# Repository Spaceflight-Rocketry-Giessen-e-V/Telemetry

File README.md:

# ASCENT Experimental Rocket Telemetry System

|</p> | </p></p>|
|---|---|
|<p align="center">[The Onboard System](/onboard/)</p>|<p align="center">[The Groundstation System](/groundstation/)</p>|

---

## Overview

The ASCENT telemetry system is part of the ASCENT flight computer of the student rocketry club [Spaceflight Rocketry Gießen e.V.](https://sprog-ev.de/en/), which is being developed for the PIPE and ARCHER experimental rockets.
This dual-frequency 169/869 MHz telemetry system based on Radiocrafts RC232 radio modules allows bidirectional data exchange between rockets and groundstations with a range of 20 km and a minimum data rate of 1.2 kbps.
The design can easily be adapted for uses outside of rocketry like Smart Home or RC.

## Basic Functionality

- Receiving flight data from the rocket
- Sending radio commands to the rocket
- Displaying live telemetry on a serial monitor or UI

## Actual Performance

In January 2026, we performed our first long range test over a distance of 2 km. Despite poor weather conditions and objects inside the first Fresnel zone, the received signal strength was on par with the theoretical maximum without any unaccounted losses. This test ruled out major design flaws.

This excellent performance was confirmed by multiple medium range tests.

In April 2026, the system was successfully tested on the PIPE 2 rocket to an altitude of 350 m and experienced no link issues during the whole flight.

---

## Repository Contents

This repository contains all files necessary to reproduce the telemetry system, including hardware, firmware, software, and documentation.

### 1. Antenna Hardware

So far, this repository includes [design files](/groundstation/antenna/helical/) and [assembly instructions](/docs/helical_antenna_assembly_manual.md) for our helical 869 MHz groundstation antenna.

We also do our own FDTD-simulations which can be found [here](groundstation/antenna/helical/Simulation/Helical_Antenna.m).

Currently, we are developing an 869 MHz QFH antenna.

### 2. Electronics Hardware

The telemetry system is based on separate [onboard](/onboard/pcb/) and [groundstation](/groundstation/pcb/) electronics.
The groundstation uses a modular approach with a [motherboard](/groundstation/pcb/Motherboard/) to which up to four [daughterboards](/groundstation/pcb/Daughterboard/) with radio modules can be connected.

The repository includes for each system the KiCad design files including custom component schematic, footprint, and 3D model libraries, the PDF schematic, the Gerber production files, the bill of material (BOM) and an interactive BOM (iBOM). 
Renderings, images, and 3D models of the electronics are also included.

The [onboard mounting structure](/onboard/mounting%20structure/), the [motherboard and daughterboard casings](/groundstation/casing/) are included separately.

### 3. Firmware

- [Onboard Firmware](/onboard/firmware/)
- [Groundstation Firmware](/groundstation/firmware/) 
- [Radiocrafts RC17xHP-RC232 Library](/libraries/Radiocrafts_RC17xxHP_RC232/)
- [Dynamic Package Codec (Encoding/Decoding) Library](/libraries/DynamicPacketCodec/)
- [Firmware Functions/Classes Reference](https://spaceflight-rocketry-giessen-e-v.github.io/Telemetry/)

### 4. Groundstation UI Software

[Python-based software](/groundstation/gui/) to display live telemetry data on a modern, minimalistic interface with the ability to store flight data and send radio commands. 

Widgets include a GNSS map view, a height plot over time, a acceleration plot over time, a battery voltage indicator with visual warnings, a connection quality indicator with visual warnings and a status event indicator.

### 5. Documentation

- [User Manual](/docs/user_manual.md) and [Operations Cheatsheet](/docs/operations_cheatsheet.md)
- [Design Overview/Rationals](/docs/design_overview.md)
- Documentation of the [Packet Structure](/docs/packet_structure.md) and the [Linkbudget Calculation](/docs/linkbudget.ipynb)
- [And more...](/docs/)

---

## Legal Notice

Please note that radio systems may be subject to local regulations. Ensure that any testing or deployment of these systems complies with national and regional laws regarding RF transmission. The project maintainers are not responsible for misuse or regulatory violations.  

## License

Copyright Spaceflight Rocketry Giessen e.V. 2026<br />
This source describes Open Hardware and is licensed under the CERN-OHL-S v2.<br />
You may redistribute and modify this source and make products using it under the terms of the [CERN-OHL-S v2 or any later version](LICENSE).<br />
This source is distributed WITHOUT ANY EXPRESS OR IMPLIED WARRANTY, INCLUDING OF MERCHANTABILITY, SATISFACTORY QUALITY AND FITNESS FOR A PARTICULAR PURPOSE. Please see the CERN-OHL-S v2 for applicable conditions.<br />
Source location: https://github.com/Spaceflight-Rocketry-Giessen-e-V/Telemetry<br />
As per CERN-OHL-S v2 section 4, should you produce hardware based on this source, you must where practicable maintain the Source Location in its documentation or license information.<br />

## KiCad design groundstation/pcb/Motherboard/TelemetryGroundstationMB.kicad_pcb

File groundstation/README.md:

# The Groundstation System

- [Motherboard Electronics Hardware](/groundstation/pcb/Motherboard/)
    - [KiCad Design Files](/groundstation/pcb/Motherboard/)
    - [PDF Schematic](/groundstation/pcb/Motherboard/TelemetryGroundstationMB_Schematic.pdf)
    - [Interactive Schematic / iBOM](/groundstation/pcb/Motherboard/TelemetryGroundstationMB_iBOM.html)
    - [BOM](/groundstation/pcb/Motherboard/TelemetryGroundstationMB_BOM.csv)
    - [Gerber Files](/groundstation/pcb/Motherboard/Production%20Files/)
    - [PCB 3D Model](/groundstation/pcb/Motherboard/TelemetryGroundstationMB.step)
    - [PCB Images](/groundstation/pcb/Motherboard/images/)
- [Daughterboard Electronics Hardware](/groundstation/pcb/Daughterboard/)
    - [KiCad Design Files](/groundstation/pcb/Daughterboard/)
    - [PDF Schematic](/groundstation/pcb/Daughterboard/TelemetryGroundstationDB_Schematic.pdf)
    - [Interactive Schematic / iBOM](/groundstation/pcb/Daughterboard/TelemetryGroundstationDB_iBOM.html)
    - [BOM](/groundstation/pcb/Daughterboard/TelemetryGroundstationDB_BOM.csv)
    - [Gerber Files](/groundstation/pcb/Daughterboard/Production%20Files/)
    - [PCB 3D Model](/groundstation/pcb/Daughterboard/TelemetryGroundstationDB.step)
    - [PCB Images](/groundstation/pcb/Daughterboard/images/)
- [Electronics Casings](/groundstation/casing/)
    - [Motherboard Casing](/groundstation/casing/Motherboard)
    - [Daughterboard Casing](/groundstation/casing/Daughterboard)
- [Firmware](/groundstation/firmware/)
- [869 MHz Helical Antenna](/groundstation/antenna/helical/)
    - [Design Files](/groundstation/antenna/helical/)
    - [Design Guide](/docs/helical_antenna_design_guide.ipynb)
    - [Assembly Manual](/docs/helical_antenna_assembly_manual.md)
    - [Antenna 3D Model](/groundstation/antenna/helical/Antenna%20Assembly.step)
    - [Antenna Images](/groundstation/antenna/helical/images/)
    - [Simulation](/groundstation/antenna/helical/Simulation/)
    - [Simulation Guide](/docs/helical_antenna_simulation_guide.md)
- [Serial Monitor Configuration File](/groundstation/Coolterm_SerialMonitor_Settings.CoolTermSettings)
- [Graphical User Interface](/groundstation/gui/)

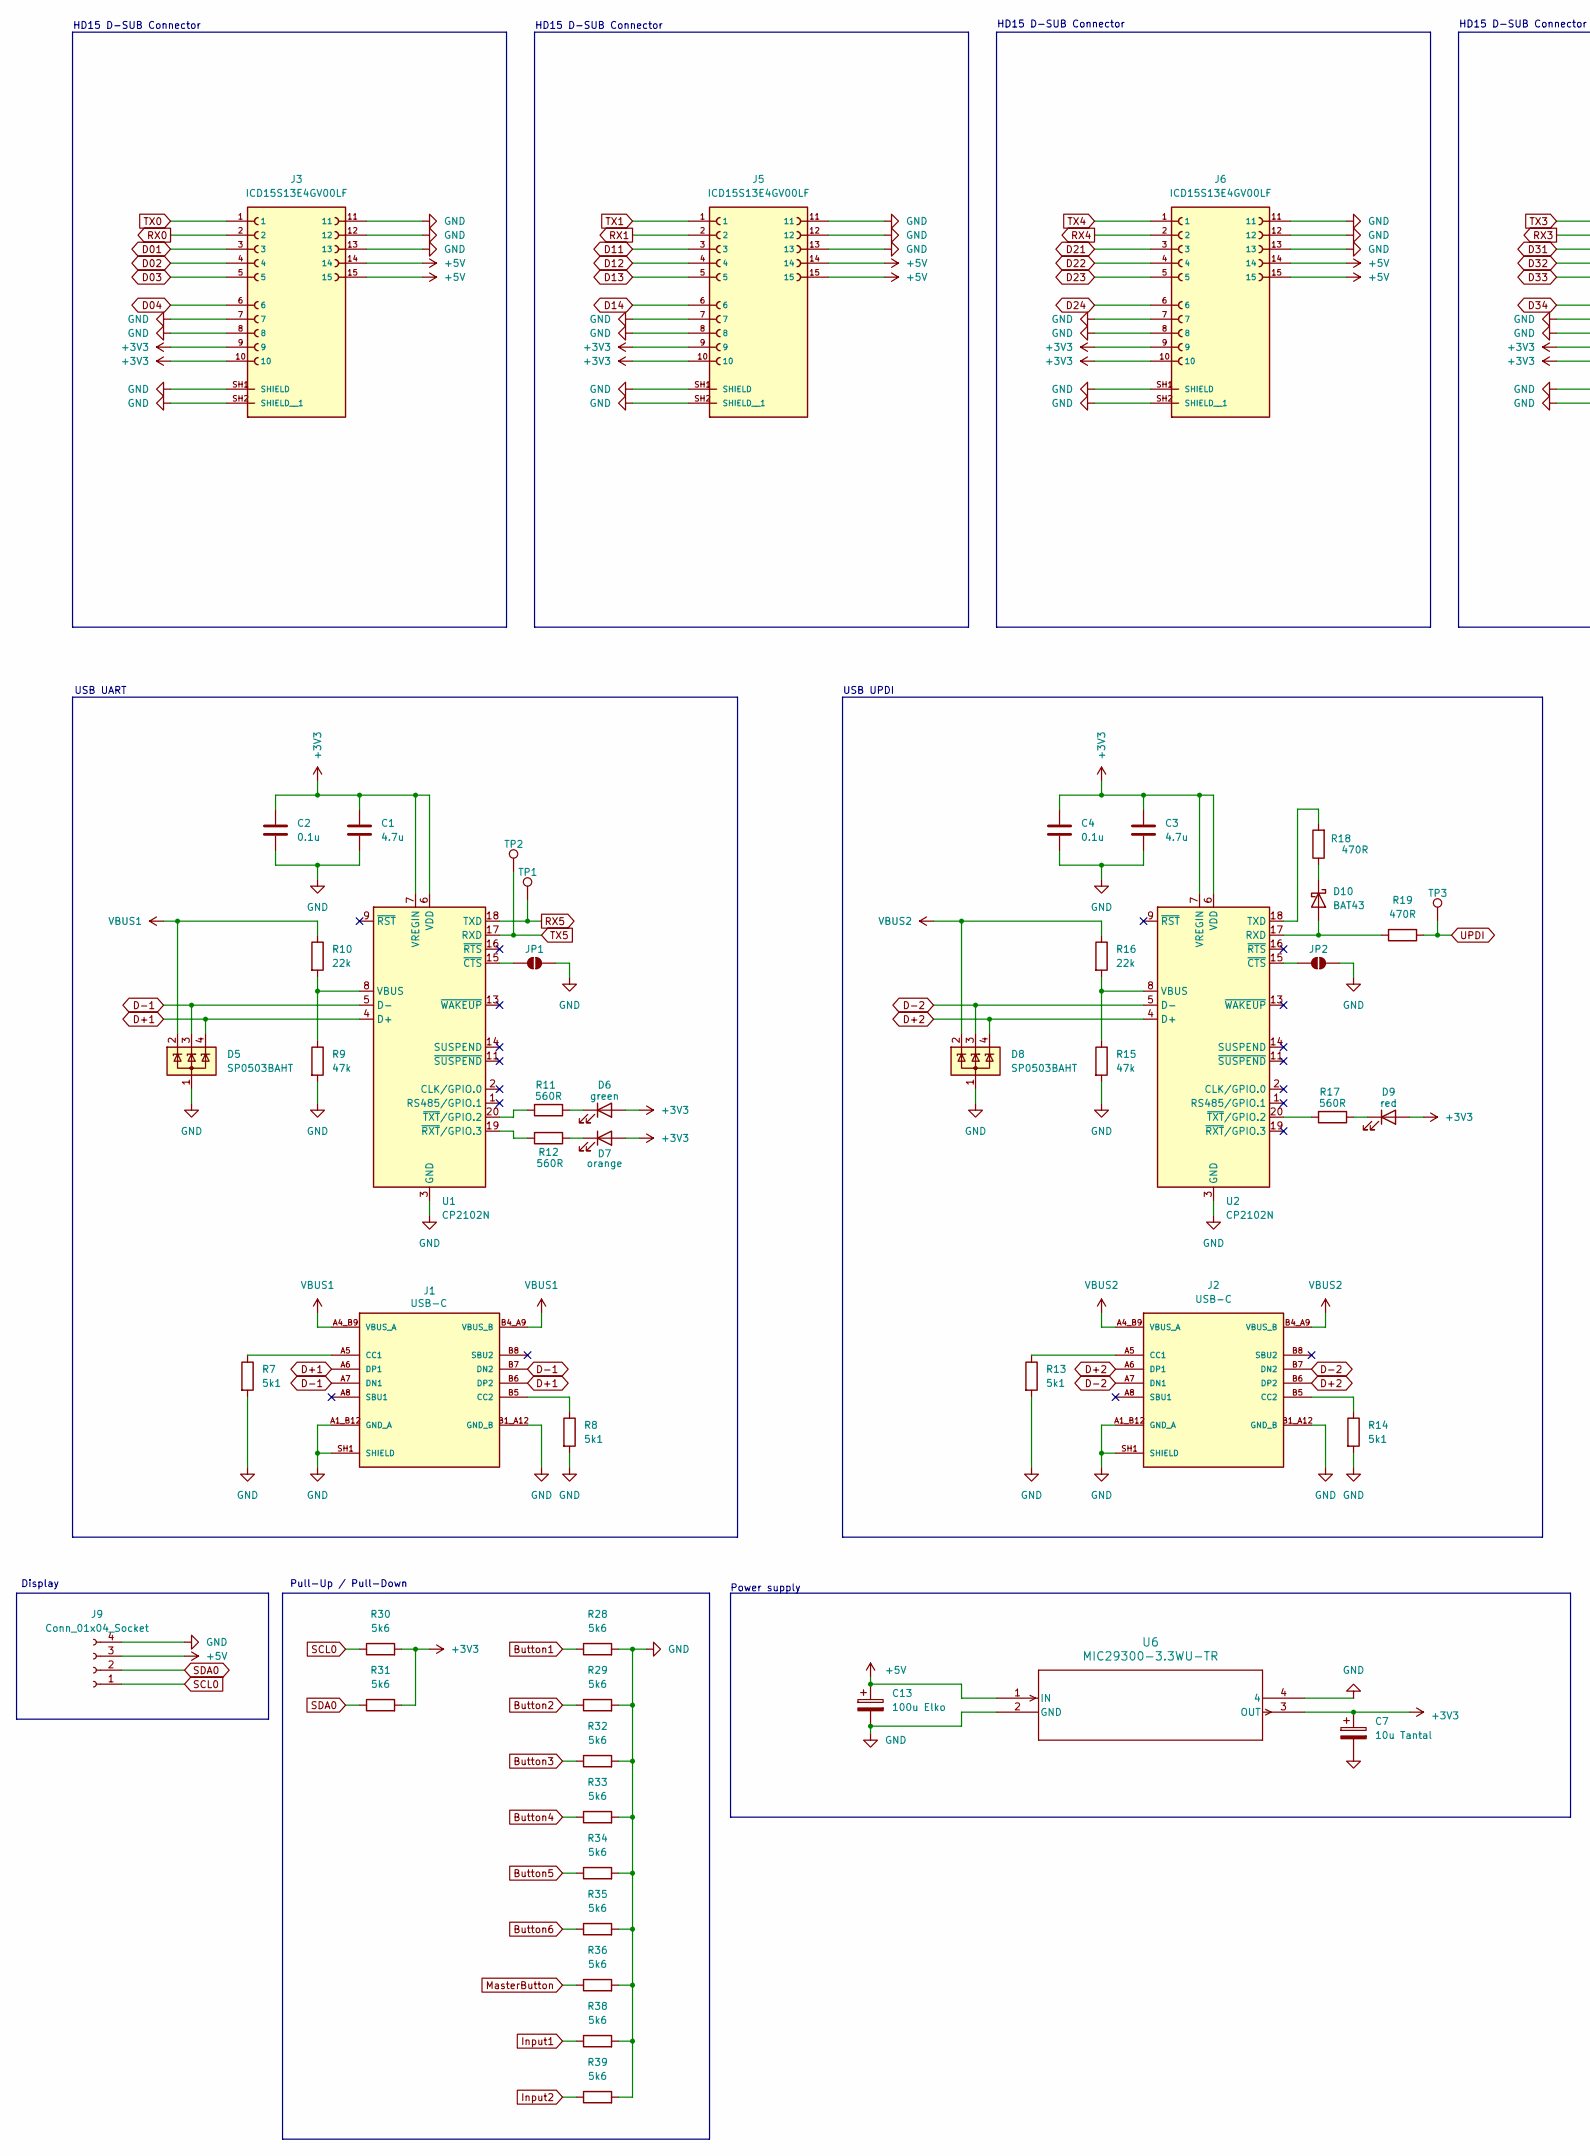
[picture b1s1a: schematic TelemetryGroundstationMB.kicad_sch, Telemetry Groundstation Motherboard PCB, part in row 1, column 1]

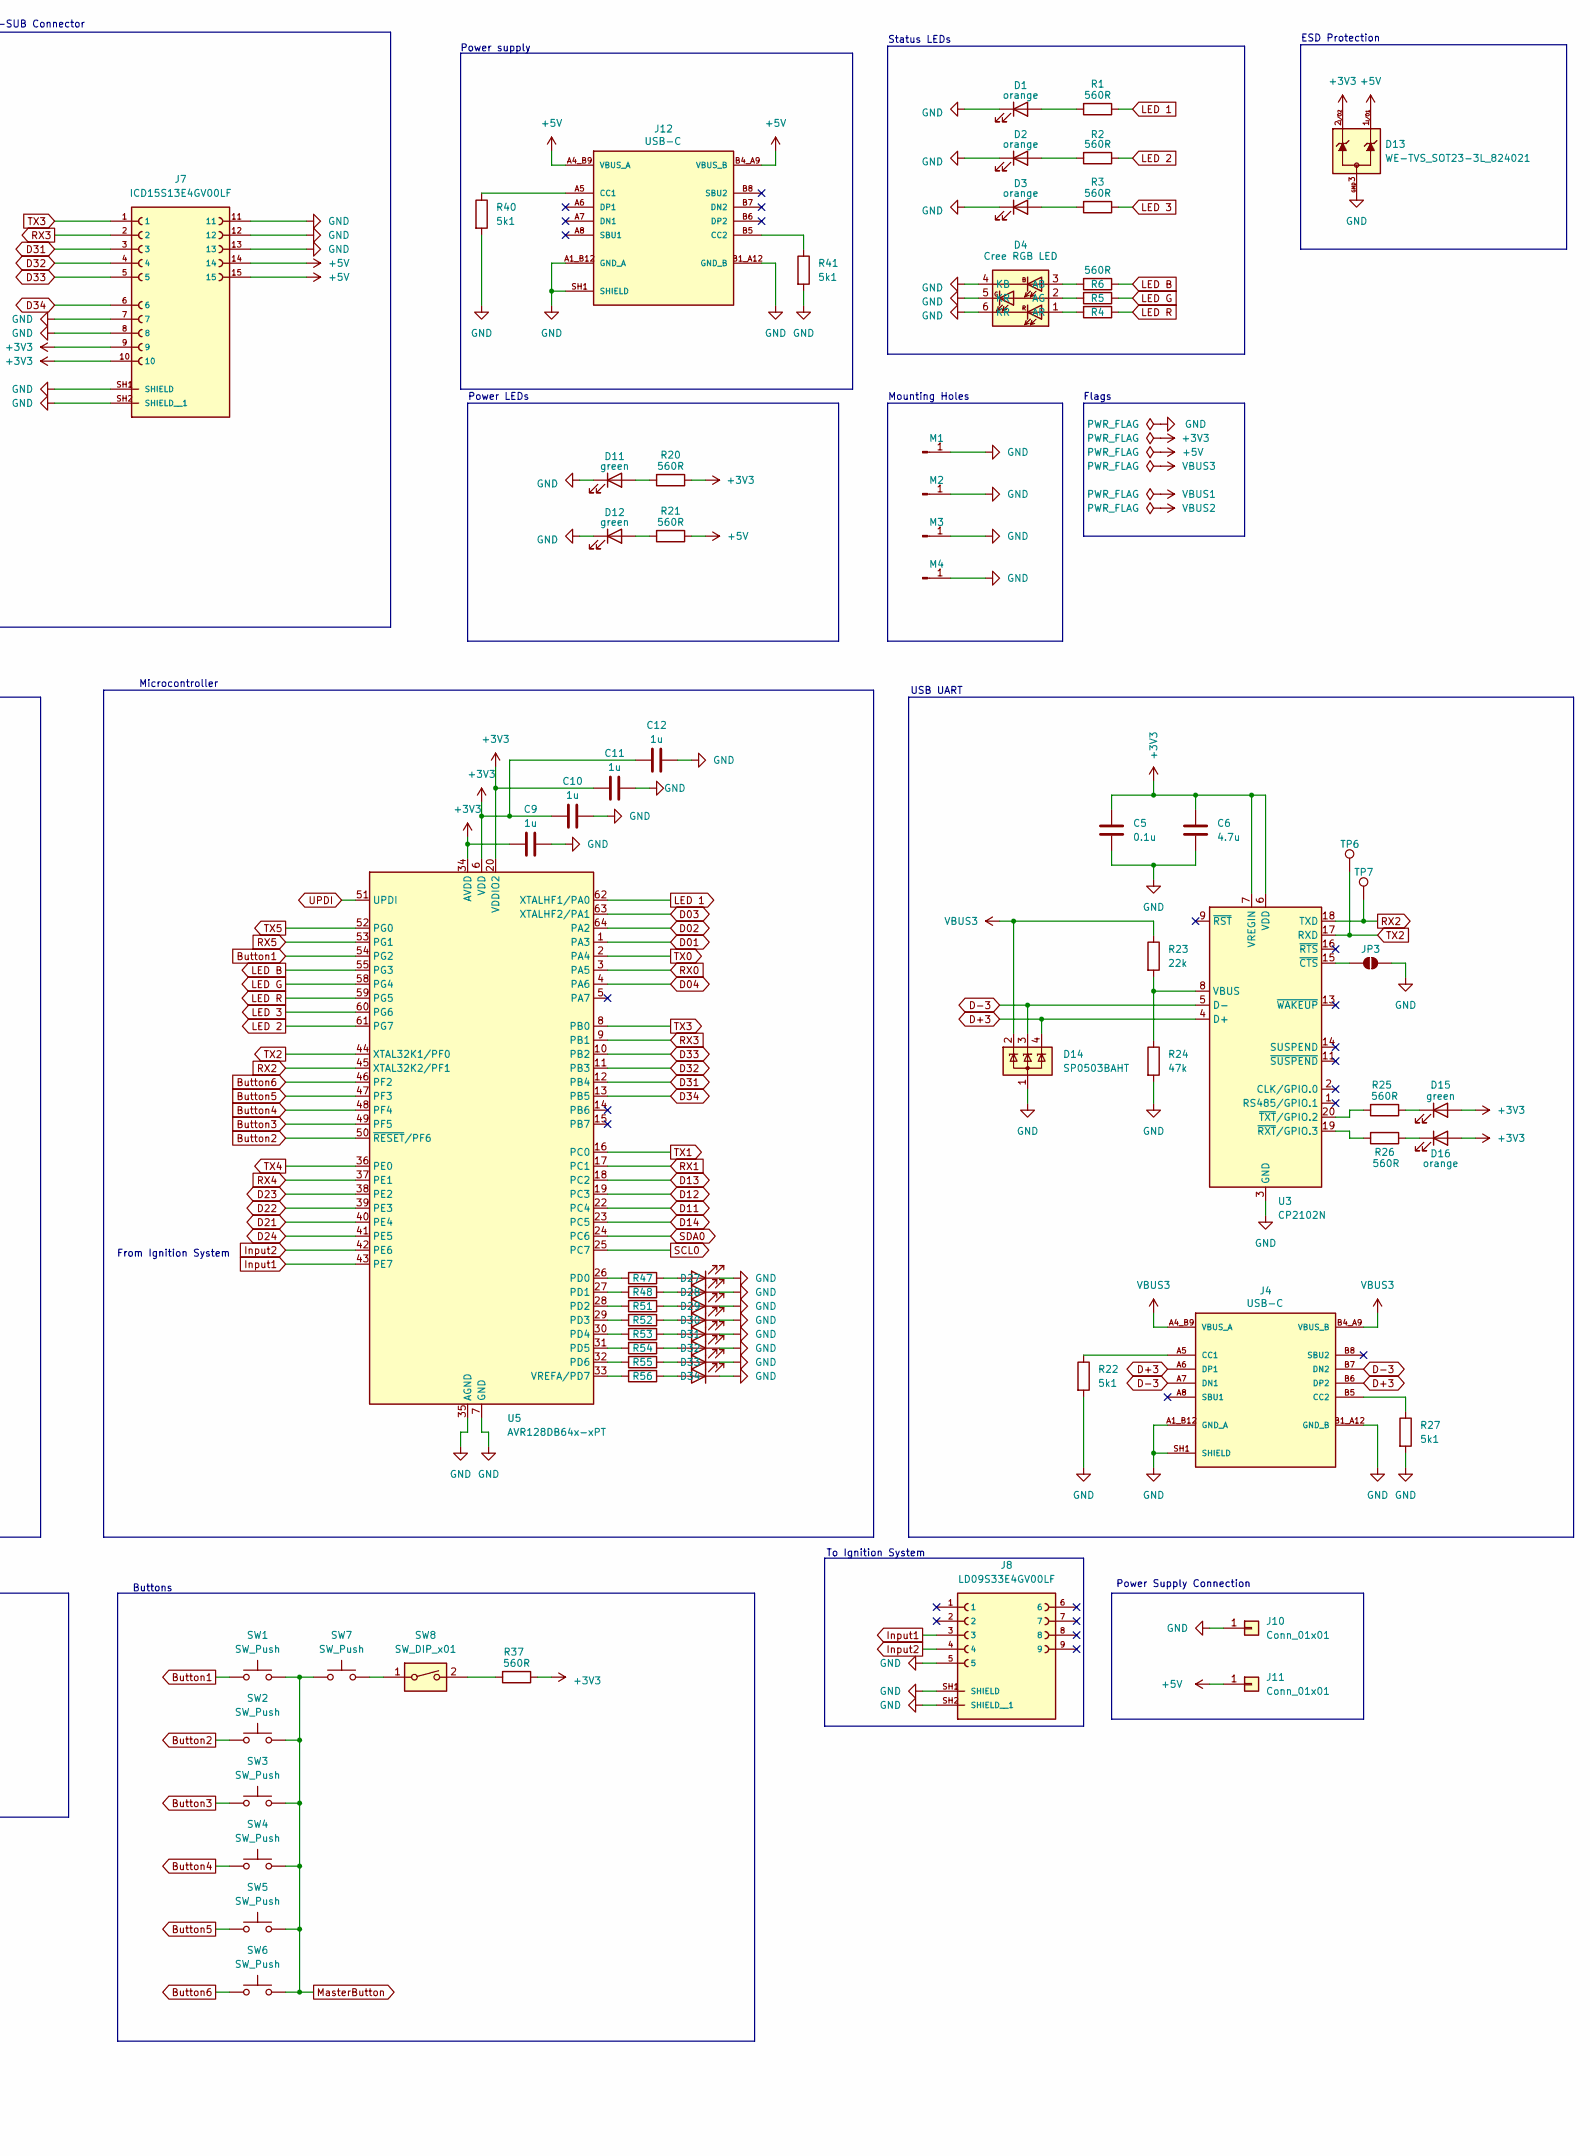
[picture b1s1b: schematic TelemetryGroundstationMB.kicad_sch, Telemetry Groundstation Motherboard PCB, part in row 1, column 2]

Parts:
C1, C3, C6: 4.7u; C_0805_2012Metric_Pad1.18x1.45mm_HandSolder
C2, C4, C5: 0.1u; C_0805_2012Metric_Pad1.18x1.45mm_HandSolder
C7: 10u Tantal; CAPMP3216X180N
C9, C10, C11, C12: 1u; C_0805_2012Metric_Pad1.18x1.45mm_HandSolder
C13: 100u Elko; CP_Radial_D6.3mm_P2.50mm
D1, D2, D3, D7, D16, D27, D28, D29, D30, D31, D32, D33, D34: orange; LED_0805_2012Metric_Pad1.15x1.40mm_HandSolder
D4: Cree RGB LED
D5, D8, D14: SP0503BAHT; SOT-143
D6, D11, D12, D15: green; LED_0805_2012Metric_Pad1.15x1.40mm_HandSolder
D9: red; LED_0805_2012Metric_Pad1.15x1.40mm_HandSolder
D10: BAT43; D_SOD-123
D13: WE-TVS_SOT23-3L_824021; SOT-23-3
J1, J2, J4, J12: USB-C; GCT_USB4216-03-A_REVA; PARTREV A; DigiKey_Part_Number 2073-USB4215-03-ACT-ND
J3, J5, J6, J7: ICD15S13E4GV00LF; AMPHENOL_ICD15S13E4GV00LF[1]; PARTREV G
J8: LD09S33E4GV00LF; AMPHENOL_LD09S33E4GV00LF; PARTREV B
J9: Conn_01x04_Socket; PinSocket_1x04_P2.54mm_Vertical
J10: Conn_01x01; Banana_CT3151-0
J11: Conn_01x01; Banana_CT3151-2
JP1, JP2, JP3: SolderJumper_2_Open; Solder Jumper
M1, M2, M3, M4: M4 Mounting Hole
R1, R2, R3, R4, R5, R6, R11, R12, R17, R20, R21, R25, R26, R37, R47, R48, R51, R52, R53, R54, R55, R56: 560R; R_0805_2012Metric_Pad1.20x1.40mm_HandSolder
R7, R8, R13, R14, R22, R27, R40, R41: 5k1; R_0805_2012Metric_Pad1.20x1.40mm_HandSolder
R9, R15, R24: 47k; R_0805_2012Metric_Pad1.20x1.40mm_HandSolder
R10, R16, R23: 22k; R_0805_2012Metric_Pad1.20x1.40mm_HandSolder
R18, R19: 470R; R_0805_2012Metric_Pad1.20x1.40mm_HandSolder
R28, R29, R30, R31, R32, R33, R34, R35, R36, R38, R39: 5k6; R_0805_2012Metric_Pad1.20x1.40mm_HandSolder
SW1, SW2, SW3, SW4, SW5, SW6, SW7: SW_Push; PinSocket_1x02_P2.54mm_Vertical
SW8: SW_DIP_x01; PinSocket_1x02_P2.54mm_Vertical
TP1, TP2, TP3, TP6, TP7: TestPoint; Test Point
U1, U2, U3: CP2102N; QFN20_CP2102N_SIL
U5: AVR128DB64x-xPT; TQFP-64_10x10mm_P0.5mm
U6: MIC29300-3.3WU-TR; MIC29300

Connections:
+3V3: C1.1, C2.1, C3.1, C4.1, C5.1, C6.1, C7.1, C9.1, C10.1, C11.2, C12.2, D6.2 (A), D7.2 (A), D9.2 (A), D13.2, D15.2 (A), D16.2 (A), J3.9, J3.10, J5.9, J5.10, J6.9, J6.10, J7.9, J7.10, R20.1, R30.2, R31.2, R37.1, U1.6 (VDD), U1.7 (VREGIN), U2.6 (VDD), U2.7 (VREGIN), U3.6 (VDD), U3.7 (VREGIN), U5.6 (VDD), U5.20 (VDDIO2), U5.34 (AVDD), U5.56 (VDD), U6.3 (OUT)
+5V: C13.1, D13.1, J3.14, J3.15, J5.14, J5.15, J6.14, J6.15, J7.14, J7.15, J9.3, J11.1, J12.A4_B9 (VBUS_A), J12.B4_A9 (VBUS_B), R21.1, U6.1 (IN)
Button1: R28.1, SW1.1, U5.54 (PG2)
Button2: R29.1, SW2.1, U5.50 (~RESET/PF6)
Button3: R32.1, SW3.1, U5.49 (PF5)
Button4: R33.1, SW4.1, U5.48 (PF4)
Button5: R34.1, SW5.1, U5.47 (PF3)
Button6: R35.1, SW6.1, U5.46 (PF2)
D01: J3.3, U5.1 (PA3)
D02: J3.4, U5.64 (PA2)
D03: J3.5, U5.63 (XTALHF2/PA1)
D04: J3.6, U5.4 (PA6)
D11: J5.3, U5.22 (PC4)
D12: J5.4, U5.19 (PC3)
D13: J5.5, U5.18 (PC2)
D14: J5.6, U5.23 (PC5)
D21: J6.3, U5.40 (PE4)
D22: J6.4, U5.39 (PE3)
D23: J6.5, U5.38 (PE2)
D24: J6.6, U5.41 (PE5)
D31: J7.3, U5.12 (PB4)
D32: J7.4, U5.11 (PB3)
D33: J7.5, U5.10 (PB2)
D34: J7.6, U5.13 (PB5)
D+1: D5.4 (K), J1.A6 (DP1), J1.B6 (DP2), U1.4 (D+)
D+2: D8.4 (K), J2.A6 (DP1), J2.B6 (DP2), U2.4 (D+)
D+3: D14.4 (K), J4.A6 (DP1), J4.B6 (DP2), U3.4 (D+)
D-1: D5.3 (K), J1.A7 (DN1), J1.B7 (DN2), U1.5 (D-)
D-2: D8.3 (K), J2.A7 (DN1), J2.B7 (DN2), U2.5 (D-)
D-3: D14.3 (K), J4.A7 (DN1), J4.B7 (DN2), U3.5 (D-)
GND: C1.2, C2.2, C3.2, C4.2, C5.2, C6.2, C7.2, C9.2, C10.2, C11.1, C12.1, C13.2, D1.1 (K), D2.1 (K), D3.1 (K), D4.4 (KB), D4.5 (KR), D4.6 (KR), D5.1 (A), D8.1 (A), D11.1 (K), D12.1 (K), D13.3, D14.1 (A), D27.1 (K), D28.1 (K), D29.1 (K), D30.1 (K), D31.1 (K), D32.1 (K), D33.1 (K), D34.1 (K), J1.A1_B12 (GND_A), J1.B1_A12 (GND_B), J1.SH1 (SHIELD), J1.SH2 (SHIELD), J1.SH3 (SHIELD), J1.SH4 (SHIELD), J2.A1_B12 (GND_A), J2.B1_A12 (GND_B), J2.SH1 (SHIELD), J2.SH2 (SHIELD), J2.SH3 (SHIELD), J2.SH4 (SHIELD), J3.7, J3.8, J3.11, J3.12, J3.13, J3.SH1 (SHIELD), J3.SH2 (SHIELD__1), J4.A1_B12 (GND_A), J4.B1_A12 (GND_B), J4.SH1 (SHIELD), J4.SH2 (SHIELD), J4.SH3 (SHIELD), J4.SH4 (SHIELD), J5.7, J5.8, J5.11, J5.12, J5.13, J5.SH1 (SHIELD), J5.SH2 (SHIELD__1), J6.7, J6.8, J6.11, J6.12, J6.13, J6.SH1 (SHIELD), J6.SH2 (SHIELD__1), J7.7, J7.8, J7.11, J7.12, J7.13, J7.SH1 (SHIELD), J7.SH2 (SHIELD__1), J8.5, J8.SH1 (SHIELD), J8.SH2 (SHIELD__1), J9.4, J10.1, J12.A1_B12 (GND_A), J12.B1_A12 (GND_B), J12.SH1 (SHIELD), J12.SH2 (SHIELD), J12.SH3 (SHIELD), J12.SH4 (SHIELD), JP1.2 (B), JP2.2 (B), JP3.2 (B), M1.1, M2.1, M3.1, M4.1, R7.2, R8.2, R9.2, R13.2, R14.2, R15.2, R22.2, R24.2, R27.2, R28.2, R29.2, R32.2, R33.2, R34.2, R35.2, R36.2, R38.2, R39.2, R40.2, R41.2, U1.3 (GND), U1.12 (GND), U1.21 (GND), U2.3 (GND), U2.12 (GND), U2.21 (GND), U3.3 (GND), U3.12 (GND), U3.21 (GND), U5.7 (GND), U5.21 (GND), U5.35 (AGND), U5.57 (GND), U6.2 (GND), U6.4, U6.5 (4), U6.6 (4)
Input1: J8.3, R38.1, U5.43 (PE7)
Input2: J8.4, R39.1, U5.42 (PE6)
LED 1: R1.1, U5.62 (XTALHF1/PA0)
LED 2: R2.1, U5.61 (PG7)
LED 3: R3.1, U5.60 (PG6)
LED B: R6.1, U5.55 (PG3)
LED G: R5.1, U5.58 (PG4)
LED R: R4.1, U5.59 (PG5)
MasterButton: R36.1, SW1.2, SW2.2, SW3.2, SW4.2, SW5.2, SW6.2, SW7.1
unnamed: D1.2 (A), R1.2
unnamed: D2.2 (A), R2.2
unnamed: D3.2 (A), R3.2
unnamed: D4.3 (AB), R6.2
unnamed: D4.2 (AG), R5.2
unnamed: D4.1 (AR), R4.2
unnamed: D6.1 (K), R11.1
unnamed: D7.1 (K), R12.1
unnamed: D9.1 (K), R17.1
unnamed: D10.2 (A), R19.2, U2.17 (RXD)
unnamed: D10.1 (K), R18.1
unnamed: D11.2 (A), R20.2
unnamed: D12.2 (A), R21.2
unnamed: D15.1 (K), R25.1
unnamed: D16.1 (K), R26.1
unnamed: D27.2 (A), R47.1
unnamed: D28.2 (A), R48.1
unnamed: D29.2 (A), R51.1
unnamed: D30.2 (A), R52.1
unnamed: D31.2 (A), R53.1
unnamed: D32.2 (A), R54.1
unnamed: D33.2 (A), R55.1
unnamed: D34.2 (A), R56.1
unnamed: J1.A5 (CC1), R7.1
unnamed: J1.B5 (CC2), R8.1
unnamed: J2.A5 (CC1), R13.1
unnamed: J2.B5 (CC2), R14.1
unnamed: J4.A5 (CC1), R22.1
unnamed: J4.B5 (CC2), R27.1
unnamed: J12.A5 (CC1), R40.1
unnamed: J12.B5 (CC2), R41.1
unnamed: JP1.1 (A), U1.15 (~CTS)
unnamed: JP2.1 (A), U2.15 (~CTS)
unnamed: JP3.1 (A), U3.15 (~CTS)
unnamed: R37.2, SW8.2
unnamed: SW7.2, SW8.1
unnamed: R9.1, R10.2, U1.8 (VBUS)
unnamed: R12.2, U1.19 (~RXT/GPIO.3)
unnamed: R11.2, U1.20 (~TXT/GPIO.2)
unnamed: R18.2, U2.18 (TXD)
unnamed: R15.1, R16.2, U2.8 (VBUS)
unnamed: R17.2, U2.20 (~TXT/GPIO.2)
unnamed: R23.2, R24.1, U3.8 (VBUS)
unnamed: R26.2, U3.19 (~RXT/GPIO.3)
unnamed: R25.2, U3.20 (~TXT/GPIO.2)
unnamed: R47.2, U5.26 (PD0)
unnamed: R48.2, U5.27 (PD1)
unnamed: R51.2, U5.28 (PD2)
unnamed: R52.2, U5.29 (PD3)
unnamed: R53.2, U5.30 (PD4)
unnamed: R54.2, U5.31 (PD5)
unnamed: R55.2, U5.32 (PD6)
unnamed: R56.2, U5.33 (VREFA/PD7)
RX0: J3.2, U5.3 (PA5)
RX1: J5.2, U5.17 (PC1)
RX2: TP7.1, U3.18 (TXD), U5.45 (XTAL32K2/PF1)
RX3: J7.2, U5.9 (PB1)
RX4: J6.2, U5.37 (PE1)
RX5: TP1.1, U1.18 (TXD), U5.53 (PG1)
SCL0: J9.1, R30.1, U5.25 (PC7)
SDA0: J9.2, R31.1, U5.24 (PC6)
TX0: J3.1, U5.2 (PA4)
TX1: J5.1, U5.16 (PC0)
TX2: TP6.1, U3.17 (RXD), U5.44 (XTAL32K1/PF0)
TX3: J7.1, U5.8 (PB0)
TX4: J6.1, U5.36 (PE0)
TX5: TP2.1, U1.17 (RXD), U5.52 (PG0)
UPDI: R19.1, TP3.1, U5.51 (UPDI)
VBUS1: D5.2 (K), J1.A4_B9 (VBUS_A), J1.B4_A9 (VBUS_B), R10.1
VBUS2: D8.2 (K), J2.A4_B9 (VBUS_A), J2.B4_A9 (VBUS_B), R16.1
VBUS3: D14.2 (K), J4.A4_B9 (VBUS_A), J4.B4_A9 (VBUS_B), R23.1

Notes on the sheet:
HD15 D-SUB Connector
Power Supply Connection
Pull-Up / Pull-Down
Power supply
Microcontroller
Flags
USB UPDI
USB UART
Status LEDs
Mounting Holes
Power LEDs
Display
ESD Protection
To Ignition System
From Ignition System
Buttons

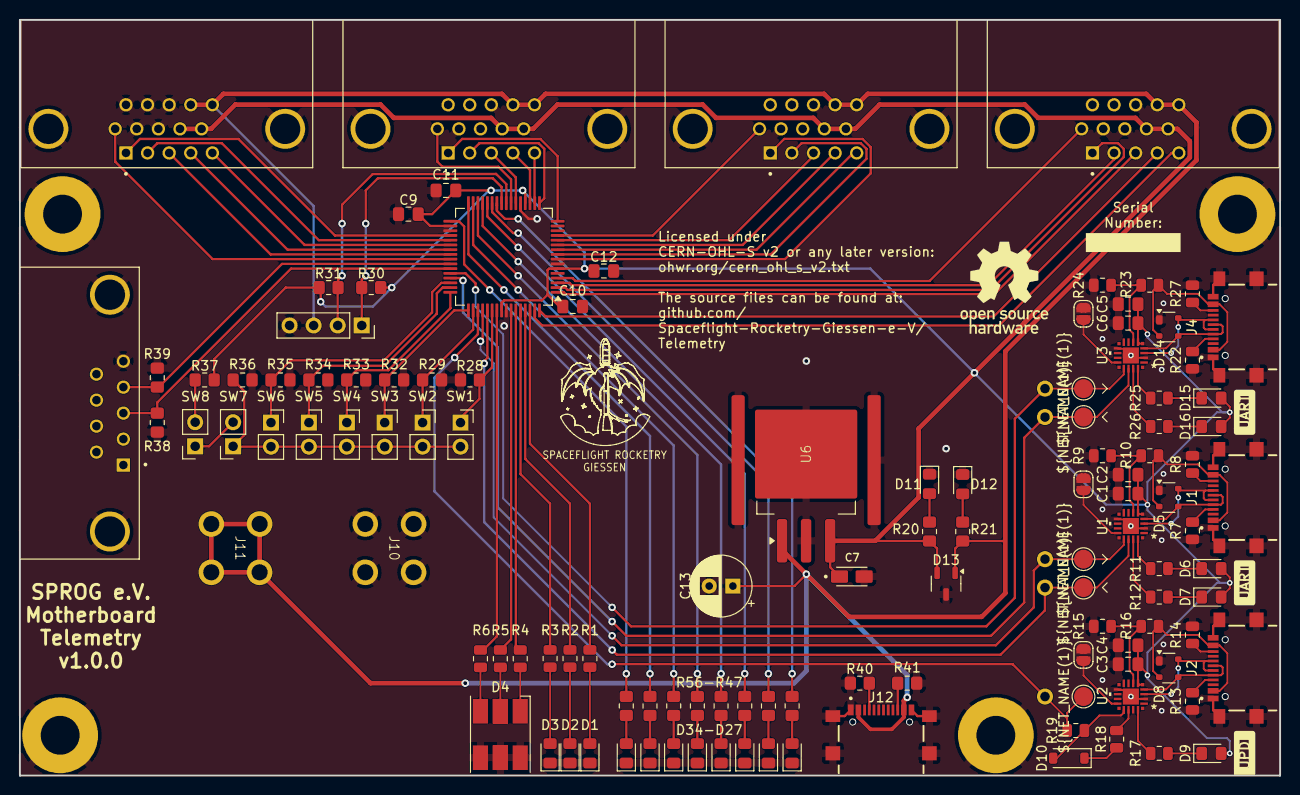
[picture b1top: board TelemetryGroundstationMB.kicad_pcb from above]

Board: 2 copper layers, 133.0 x 79.8 mm, 122 parts (0 on the bottom side), 111 nets.

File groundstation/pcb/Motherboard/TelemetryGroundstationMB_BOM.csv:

"Reference","Qty","Value","Footprint","DNP","Purchase-URL"
"C1,C3,C6","3","4.7 uF","Capacitor_SMD:C_0805_2012Metric_Pad1.18x1.45mm_HandSolder","",""
"C2,C4,C5","3","0.1 uF","Capacitor_SMD:C_0805_2012Metric_Pad1.18x1.45mm_HandSolder","",""
"C7","1","10uF Tantal","Footprints:CAPMP3216X180N","",""
"C9,C10,C11,C12","4","1 uF","Capacitor_SMD:C_0805_2012Metric_Pad1.18x1.45mm_HandSolder","","https://www.digikey.de/de/products/detail/samsung-electro-me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"
"C13","1","100uF Elko","Capacitor_THT:CP_Radial_D6.3mm_P2.50mm","",""
"D1,D2,D3,D7,D16,D27,D28,D29,D30,D31,D32,D33,D34","13","orange","LED_SMD:LED_0805_2012Metric_Pad1.15x1.40mm_HandSolder","","https://www.digikey.de/de/products/detail/liteon/LTST-C170KF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"
"D4","1","Cree RGB LED","Footprints:Cree RGB LED","",""
"D5,D8,D14","3","SP0503BAHT","Package_TO_SOT_SMD:SOT-143","",""
"D6,D11,D12,D15","4","green","LED_SMD:LED_0805_2012Metric_Pad1.15x1.40mm_HandSolder","",""
"D9","1","red","LED_SMD:LED_0805_2012Metric_Pad1.15x1.40mm_HandSolder","",""
"D10","1","BAT43","Diode_SMD:D_SOD-123","",""
"D13","1","WE-TVS_SOT23-3L_824021","Package_TO_SOT_SMD:SOT-23-3","",""
"J1,J2,J4,J12","4","USB-C","Footprints:GCT_USB4216-03-A_REVA","",""
"J3,J5,J6,J7","4","ICD15S13E4GV00LF","Footprints:AMPHENOL_ICD15S13E4GV00LF[1]","",""
"J8","1","LD09S33E4GV00LF","Footprints:AMPHENOL_LD09S33E4GV00LF","",""
"J9","1","Conn_01x04_Socket","Connector_PinSocket_2.54mm:PinSocket_1x04_P2.54mm_Vertical","",""
"J10,J11","2","Conn_01x01","Footprints:Banana_CT3151-0","",""
"M1,M2,M3,M4","4","M4 Mounting Hole","Footprints:M4 Mounting Hole","",""
"R1,R2,R3,R4,R5,R6,R11,R12,R17,R20,R21,R25,R26,R37,R47,R48,R51,R52,R53,R54,R55,R56","22","560 Ohm","Resistor_SMD:R_0805_2012Metric_Pad1.20x1.40mm_HandSolder","","https://www.digikey.de/de/products/detail/yageo/RC0805JR-072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"
"R7,R8,R13,R14,R22,R27,R40,R41","8","5k1","Resistor_SMD:R_0805_2012Metric_Pad1.20x1.40mm_HandSolder","",""
"R9,R15,R24","3","47k","Resistor_SMD:R_0805_2012Metric_Pad1.20x1.40mm_HandSolder","",""
"R10,R16,R23","3","22k","Resistor_SMD:R_0805_2012Metric_Pad1.20x1.40mm_HandSolder","",""
"R18,R19","2","470 Ohm","Resistor_SMD:R_0805_2012Metric_Pad1.20x1.40mm_HandSolder","",""
"R28,R29,R30,R31,R32,R33,R34,R35,R36,R38,R39","11","5k6","Resistor_SMD:R_0805_2012Metric_Pad1.20x1.40mm_HandSolder","",""
"SW1,SW2,SW3,SW4,SW5,SW6,SW7","7","SW_Push","Connector_PinSocket_2.54mm:PinSocket_1x02_P2.54mm_Vertical","",""
"SW8","1","SW_DIP_x01","Connector_PinSocket_2.54mm:PinSocket_1x02_P2.54mm_Vertical","",""
"TP1,TP2,TP3,TP6,TP7","5","TestPoint","Footprints:Test Point","",""
"U1,U2,U3","3","CP2102N","Footprints:QFN20_CP2102N_SIL","",""
"U5","1","AVR128DB64x-xPT","Package_QFP:TQFP-64_10x10mm_P0.5mm","","https://www.digikey.de/de/products/detail/microchip-technolo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"
"U6","1","MIC29300-3.3WU-TR","Footprints:MIC29300","",""

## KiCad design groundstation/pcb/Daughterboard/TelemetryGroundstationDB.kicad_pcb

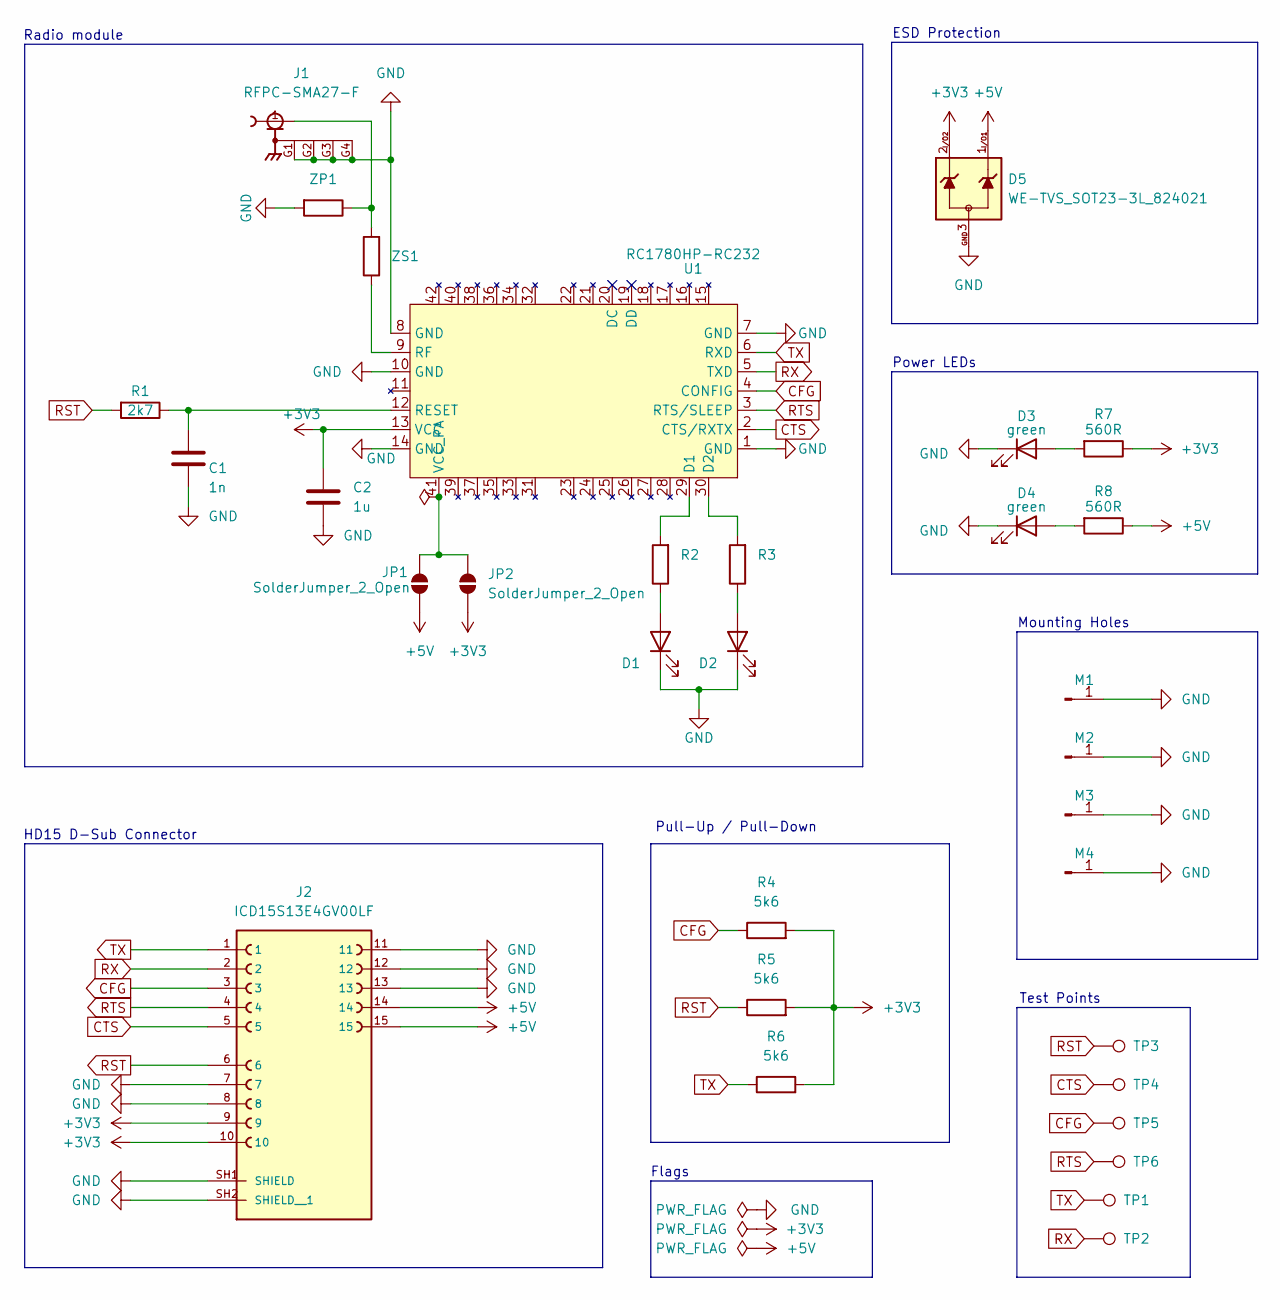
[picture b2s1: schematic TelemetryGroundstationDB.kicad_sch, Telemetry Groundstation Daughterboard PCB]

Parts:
C1: 1n; C_0805_2012Metric_Pad1.18x1.45mm_HandSolder
C2: 1u; C_0805_2012Metric_Pad1.18x1.45mm_HandSolder
D1, D3, D4: green; LED_0805_2012Metric_Pad1.15x1.40mm_HandSolder
D2: yellow; LED_0805_2012Metric_Pad1.15x1.40mm_HandSolder
D5: WE-TVS_SOT23-3L_824021; SOT-23-3
J1: RFPC-SMA27-F; GRADCONN_RFPC-SMA27-F; PARTREV 1.0; DigiKey_Part_Number 2073-RFPC-SMA27-F-ND
J2: ICD15S13E4GV00LF; AMPHENOL_ICD15S13E4GV00LF[1]; PARTREV G
JP1, JP2: SolderJumper_2_Open; Solder Jumper
M1, M2, M3, M4: M4 Mounting Hole
R1: 2k7; R_0805_2012Metric_Pad1.20x1.40mm_HandSolder
R2, R3, R7, R8: 560R; R_0805_2012Metric_Pad1.20x1.40mm_HandSolder
R4, R5, R6: 5k6; R_0805_2012Metric_Pad1.20x1.40mm_HandSolder
TP1, TP2, TP3, TP4, TP5, TP6: TestPoint; Test Point
U1: RC1780HP-RC232; Radiocrafts RC1780HP-RC232
ZP1: R_0805_2012Metric_Pad1.20x1.40mm_HandSolder
ZS1: R_0805_2012Metric_Pad1.20x1.40mm_HandSolder

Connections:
+3V3: C2.1, D5.2, J2.9, J2.10, JP2.1 (A), R4.2, R5.2, R6.2, R7.1, U1.13 (VCC)
+5V: D5.1, J2.14, J2.15, JP1.1 (A), R8.1
CFG: J2.3, R4.1, TP5.1, U1.4 (CONFIG)
CTS: J2.5, TP4.1, U1.2 (CTS/RXTX)
GND: C1.2, C2.2, D1.1 (K), D2.1 (K), D3.1 (K), D4.1 (K), D5.3, J1.G1, J1.G2, J1.G3, J1.G4, J2.7, J2.8, J2.11, J2.12, J2.13, J2.SH1 (SHIELD), J2.SH2 (SHIELD__1), M1.1, M2.1, M3.1, M4.1, U1.1 (GND), U1.7 (GND), U1.8 (GND), U1.10 (GND), U1.14 (GND), ZP1.2
unnamed: D1.2 (A), R2.1
unnamed: D2.2 (A), R3.1
unnamed: D3.2 (A), R7.2
unnamed: D4.2 (A), R8.2
unnamed: J1.1, ZP1.1, ZS1.2
unnamed: JP1.2 (B), JP2.2 (B), U1.41 (VCC_PA)
unnamed: R2.2, U1.29 (D1)
unnamed: R3.2, U1.30 (D2)
unnamed: C1.1, R1.1, U1.12 (RESET)
unnamed: U1.9 (RF), ZS1.1
RST: J2.6, R1.2, R5.1, TP3.1
RTS: J2.4, TP6.1, U1.3 (RTS/SLEEP)
RX: J2.2, TP2.1, U1.5 (TXD)
TX: J2.1, R6.1, TP1.1, U1.6 (RXD)

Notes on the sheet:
Pull-Up / Pull-Down
Radio module
Flags
Test Points
HD15 D-Sub Connector
Mounting Holes
Power LEDs
ESD Protection

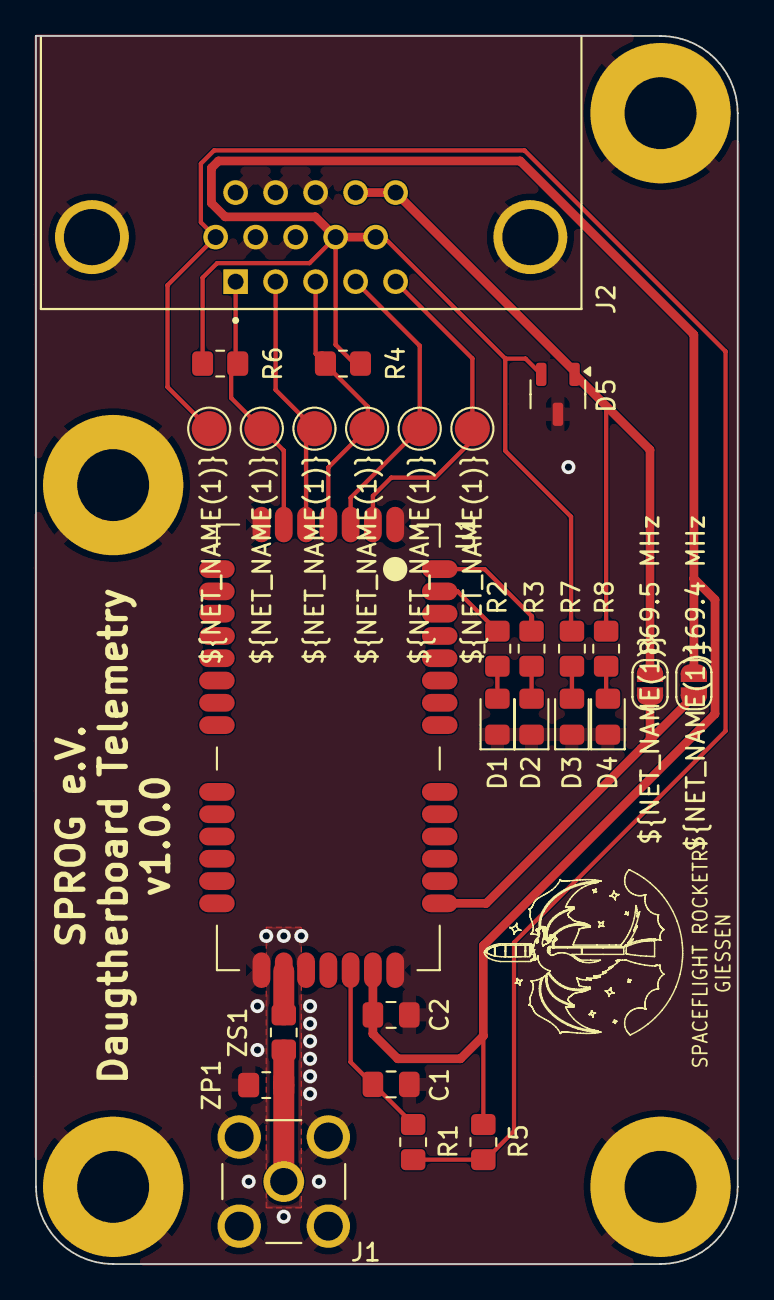
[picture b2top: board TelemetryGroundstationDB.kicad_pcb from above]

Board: 2 copper layers, 40.0 x 70.0 mm, 32 parts (0 on the bottom side), 19 nets.

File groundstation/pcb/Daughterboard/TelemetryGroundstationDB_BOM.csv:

"Reference","Qty","Value","Footprint","DNP","Purchase-URL"
"C1","1","1n","Capacitor_SMD:C_0805_2012Metric_Pad1.18x1.45mm_HandSolder","","https://www.digikey.de/de/products/detail/samsung-electro-me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"
"C2","1","1u","Capacitor_SMD:C_0805_2012Metric_Pad1.18x1.45mm_HandSolder","","https://www.digikey.de/de/products/detail/samsung-electro-me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"
"D1,D3,D4","3","green","LED_SMD:LED_0805_2012Metric_Pad1.15x1.40mm_HandSolder","","https://www.digikey.de/de/products/detail/liteon/LTST-C171KG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"
"D2","1","yellow","LED_SMD:LED_0805_2012Metric_Pad1.15x1.40mm_HandSolder","","https://www.digikey.de/de/products/detail/liteon/LTST-C170KS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"
"D5","1","WE-TVS_SOT23-3L_824021","Package_TO_SOT_SMD:SOT-23-3","","https://www.digikey.de/de/products/detail/w%C3%BCrth-elektro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"
"J1","1","RFPC-SMA27-F","Footprints:GRADCONN_RFPC-SMA27-F","","https://www.digikey.de/de/products/detail/gct/RFPC-SMA27-F/22162144"
"J2","1","ICD15S13E4GV00LF","Footprints:AMPHENOL_ICD15S13E4GV00LF[1]","","https://www.digikey.de/de/products/detail/amphenol-cs-fci/IC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"
"M1,M2,M3,M4","4","M4 Mounting Hole","Footprints:M4 Mounting Hole","","~"
"R1","1","2k7","Resistor_SMD:R_0805_2012Metric_Pad1.20x1.40mm_HandSolder","","https://www.digikey.de/de/products/detail/stackpole-electron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"
"R2,R3,R7,R8","4","560R","Resistor_SMD:R_0805_2012Metric_Pad1.20x1.40mm_HandSolder","","https://www.digikey.de/de/products/detail/stackpole-electron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"
"R4,R5,R6","3","5k6","Resistor_SMD:R_0805_2012Metric_Pad1.20x1.40mm_HandSolder","","https://www.digikey.de/de/products/detail/stackpole-electron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"
"TP1,TP2,TP3,TP4,TP5,TP6","6","TestPoint","Footprints:Test Point","","~"
"U1","1","RC1780HP-RC232","Footprints:Radiocrafts RC1780HP-RC232","","https://www.digikey.de/de/products/detail/radiocrafts-as/RC1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"
"ZP1","1","~","Resistor_SMD:R_0805_2012Metric_Pad1.20x1.40mm_HandSolder","","~"
"ZS1","1","~","Resistor_SMD:R_0805_2012Metric_Pad1.20x1.40mm_HandSolder","","~"

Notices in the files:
onboard/pcb/Telemetrie v2.kicad_pcb:
Licensed under CERN-OHL-S v2 or any later version:
ohwr.org/cern_ohl_s_v2.txt
